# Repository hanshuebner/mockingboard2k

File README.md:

# mockingboard2k - Mockingboard compatible Apple II sound card

This Mockingboard clone uses SMD parts for all modern components.  The KiCAD
project was cloned from the Apple II 32-GPIO Card by Scott Alfter.

[Schematic](mockingboard2k.pdf)

Please make sure that you're using 6522A VIAs.  6522 chips often don't work
with the Phi2 generation circuit that is present on this board.

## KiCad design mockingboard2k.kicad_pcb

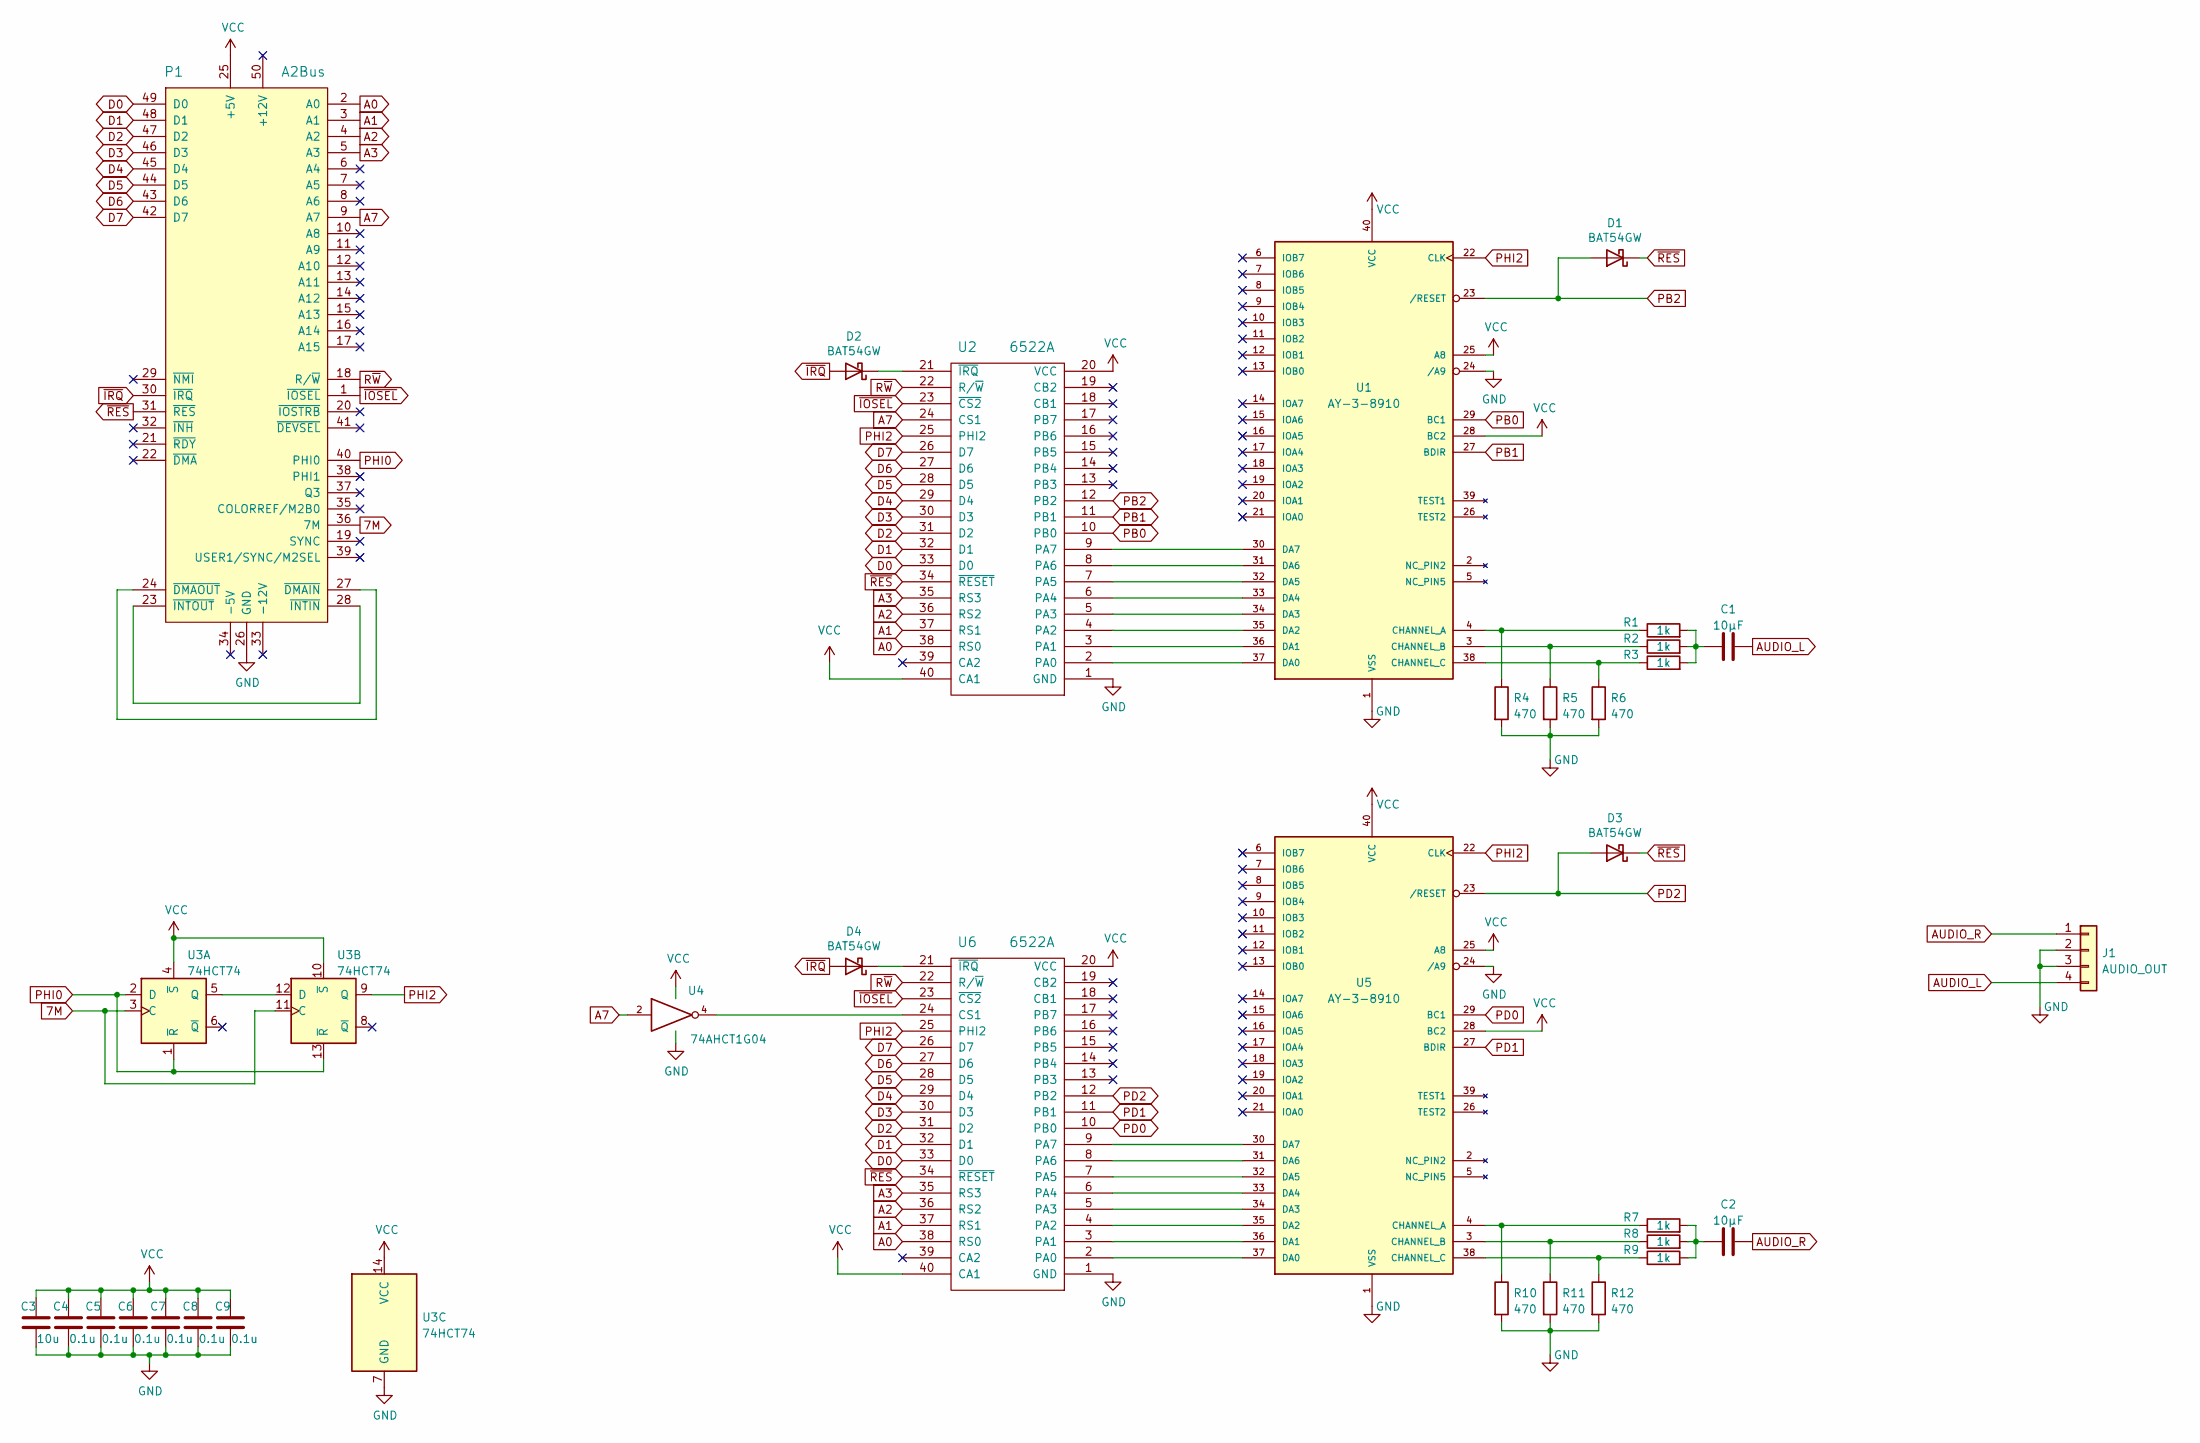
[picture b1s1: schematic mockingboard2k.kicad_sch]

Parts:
C1, C2: 10μF; C_0805_2012Metric; LCSC C2835555
C3: 10u; C_0805_2012Metric; LCSC C2830722
C4, C5, C6, C7, C8, C9: 0.1u; C_0805_2012Metric; LCSC C2830722
D1, D2, D3, D4: BAT54GW; D_SOD-123; Mfr PN BAT54GWJ; LCSC C77343
J1: AUDIO_OUT; PinSocket_1x04_P2.54mm_Horizontal
P1: A2Bus; Male_Card-Edge_50_pin__100_mil
R1, R2, R3, R7, R8, R9: 1k; R_0805_2012Metric; LCSC C325761
R4, R5, R6, R10, R11, R12: 470; R_0805_2012Metric; LCSC C269542
U1, U5: AY-3-8910; DIP-40_W15.24mm
U2, U6: 6522A; DIP-40_W15.24mm; Mfr PN W65C22S6TPG-14
U3: 74HCT74; TSSOP-14_4.4x5mm_P0.65mm; LCSC C8164
U4: 74AHCT1G04; 74AHCT1G04W5-7; LCSC C460498

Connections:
7M: P1.36 (7M), U3.3 (C), U3.11 (C)
A0: P1.2 (A0), U2.38 (RS0), U6.38 (RS0)
A1: P1.3 (A1), U2.37 (RS1), U6.37 (RS1)
A2: P1.4 (A2), U2.36 (RS2), U6.36 (RS2)
A3: P1.5 (A3), U2.35 (RS3), U6.35 (RS3)
A7: P1.9 (A7), U2.24 (CS1), U4.2
AUDIO_L: C1.2, J1.4
AUDIO_R: C2.2, J1.1
D0: P1.49 (D0), U2.33 (D0), U6.33 (D0)
D1: P1.48 (D1), U2.32 (D1), U6.32 (D1)
D2: P1.47 (D2), U2.31 (D2), U6.31 (D2)
D3: P1.46 (D3), U2.30 (D3), U6.30 (D3)
D4: P1.45 (D4), U2.29 (D4), U6.29 (D4)
D5: P1.44 (D5), U2.28 (D5), U6.28 (D5)
D6: P1.43 (D6), U2.27 (D6), U6.27 (D6)
D7: P1.42 (D7), U2.26 (D7), U6.26 (D7)
GND: C3.2, C4.2, C5.2, C6.2, C7.2, C8.2, C9.2, J1.2, J1.3, P1.26 (GND), R4.2, R5.2, R6.2, R10.2, R11.2, R12.2, U1.1 (VSS), U1.24 (/A9), U2.1 (GND), U3.7 (GND), U4.3 (GND), U5.1 (VSS), U5.24 (/A9), U6.1 (GND)
unnamed: C1.1, R1.2, R2.2, R3.2
unnamed: C2.1, R7.2, R8.2, R9.2
unnamed: D2.1 (K), U2.21 (~IRQ)
unnamed: D4.1 (K), U6.21 (~IRQ)
unnamed: P1.23 (~INTOUT), P1.28 (~INTIN)
unnamed: P1.24 (~DMAOUT), P1.27 (~DMAIN)
unnamed: R1.1, R4.1, U1.4 (CHANNEL_A)
unnamed: R2.1, R5.1, U1.3 (CHANNEL_B)
unnamed: R3.1, R6.1, U1.38 (CHANNEL_C)
unnamed: R7.1, R10.1, U5.4 (CHANNEL_A)
unnamed: R8.1, R11.1, U5.3 (CHANNEL_B)
unnamed: R9.1, R12.1, U5.38 (CHANNEL_C)
unnamed: U1.30 (DA7), U2.9 (PA7)
unnamed: U1.31 (DA6), U2.8 (PA6)
unnamed: U1.32 (DA5), U2.7 (PA5)
unnamed: U1.33 (DA4), U2.6 (PA4)
unnamed: U1.34 (DA3), U2.5 (PA3)
unnamed: U1.35 (DA2), U2.4 (PA2)
unnamed: U1.36 (DA1), U2.3 (PA1)
unnamed: U1.37 (DA0), U2.2 (PA0)
unnamed: U3.5 (Q), U3.12 (D)
unnamed: U4.4, U6.24 (CS1)
unnamed: U5.30 (DA7), U6.9 (PA7)
unnamed: U5.31 (DA6), U6.8 (PA6)
unnamed: U5.32 (DA5), U6.7 (PA5)
unnamed: U5.33 (DA4), U6.6 (PA4)
unnamed: U5.34 (DA3), U6.5 (PA3)
unnamed: U5.35 (DA2), U6.4 (PA2)
unnamed: U5.36 (DA1), U6.3 (PA1)
unnamed: U5.37 (DA0), U6.2 (PA0)
PB0: U1.29 (BC1), U2.10 (PB0)
PB1: U1.27 (BDIR), U2.11 (PB1)
PB2: D1.2 (A), U1.23 (/RESET), U2.12 (PB2)
PD0: U5.29 (BC1), U6.10 (PB0)
PD1: U5.27 (BDIR), U6.11 (PB1)
PD2: D3.2 (A), U5.23 (/RESET), U6.12 (PB2)
PHI0: P1.40 (PHI0), U3.1 (~R), U3.2 (D), U3.13 (~R)
PHI2: U1.22 (CLK), U2.25 (PHI2), U3.9 (Q), U5.22 (CLK), U6.25 (PHI2)
R~W: P1.18 (R/~W), U2.22 (R/~W), U6.22 (R/~W)
VCC: C3.1, C4.1, C5.1, C6.1, C7.1, C8.1, C9.1, P1.25 (+5V), U1.25 (A8), U1.28 (BC2), U1.40 (VCC), U2.20 (VCC), U2.40 (CA1), U3.4 (~S), U3.10 (~S), U3.14 (VCC), U4.5 (VCC), U5.25 (A8), U5.28 (BC2), U5.40 (VCC), U6.20 (VCC), U6.40 (CA1)
~IOSEL: P1.1 (~IOSEL), U2.23 (~CS2), U6.23 (~CS2)
~IRQ: D2.2 (A), D4.2 (A), P1.30 (~IRQ)
~RES: D1.1 (K), D3.1 (K), P1.31 (~RES), U2.34 (~RESET), U6.34 (~RESET)

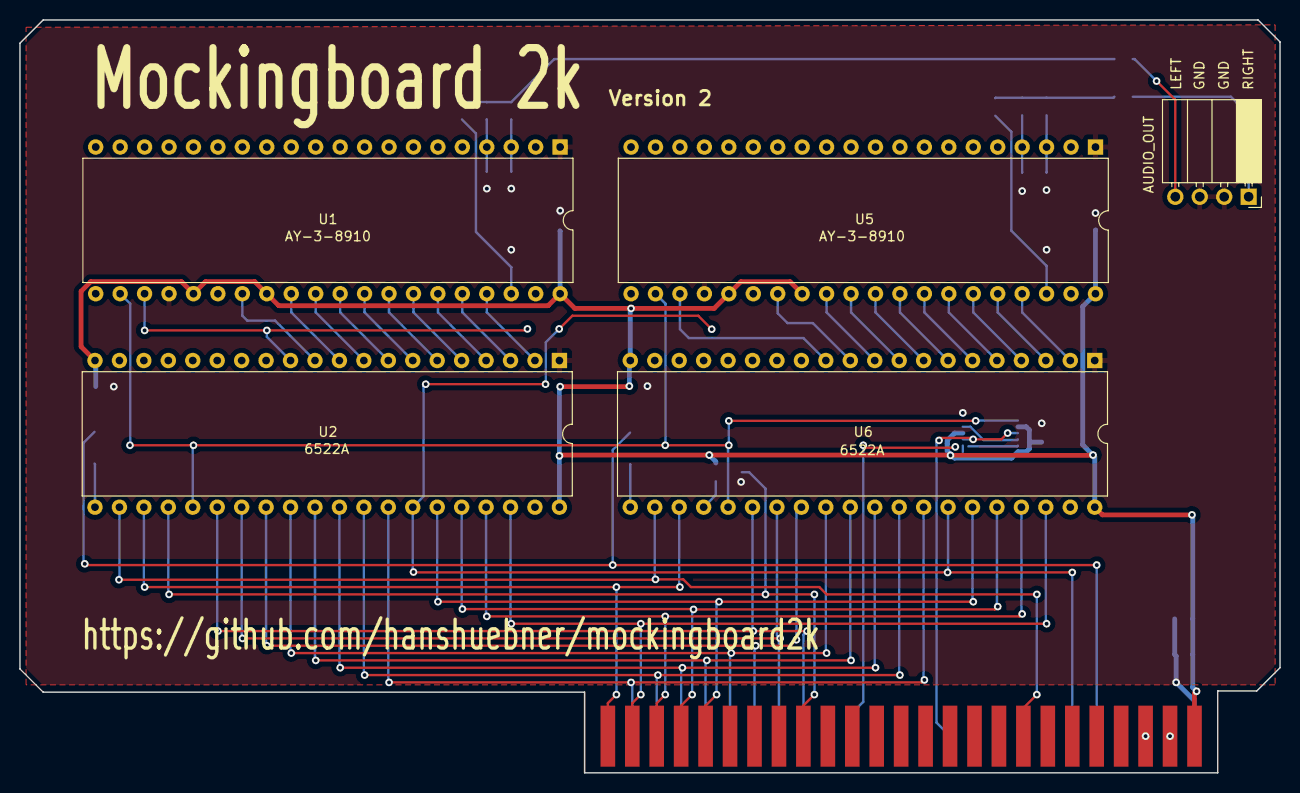
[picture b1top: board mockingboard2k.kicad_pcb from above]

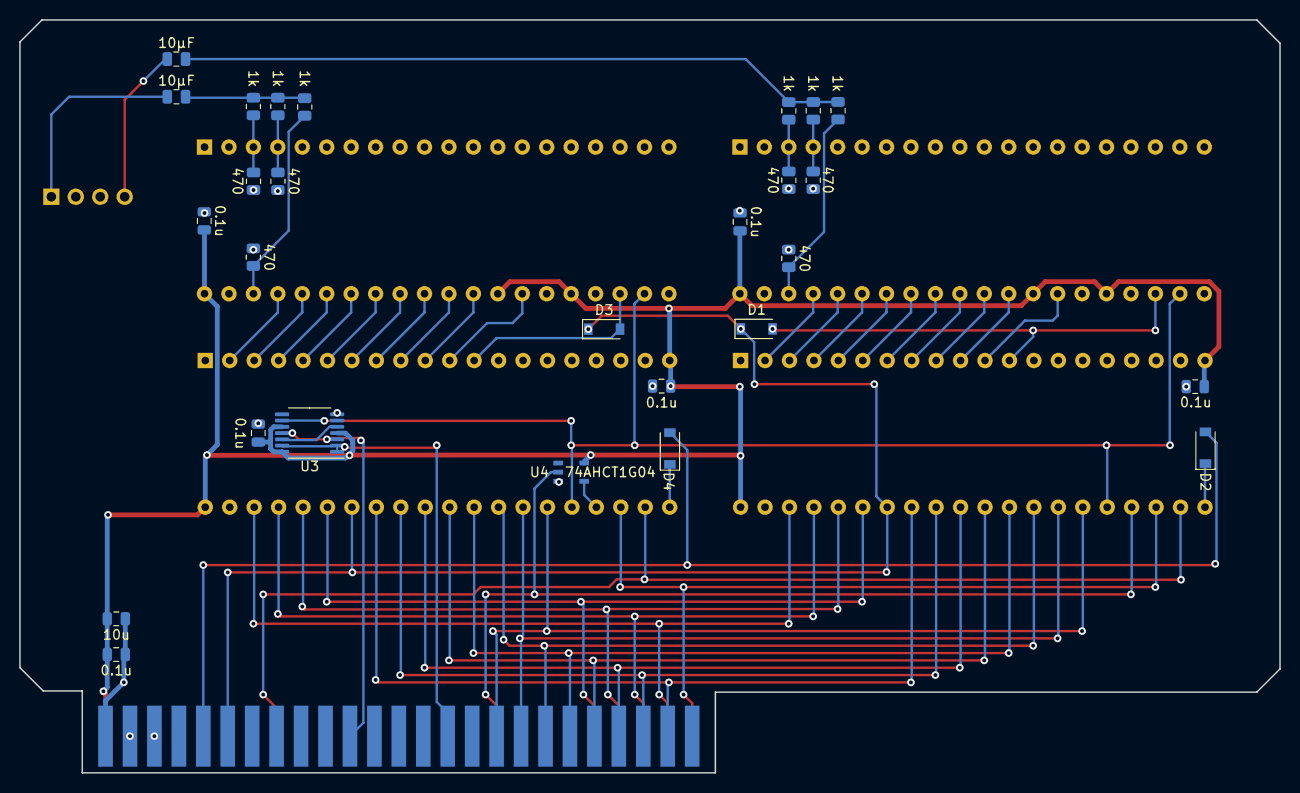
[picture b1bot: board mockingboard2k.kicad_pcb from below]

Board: 2 copper layers, 130.9 x 78.2 mm, 33 parts (27 on the bottom side), 60 nets.

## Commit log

2018-09-14 more routing
2018-09-16 routing complete
2018-09-16 shrink card a bit
2018-09-17 trim 150 mils off edge connector, generate gerbers
2018-09-17 add documentation
2018-09-17 add Schottky diodes on IRQ outputs for W65C22S
2018-09-17 add a PDF of the schematic
2018-09-18 edge connector revised
2022-03-26 Mockingboard with delay-based Phi2
2022-03-26 All-SMD version
2022-03-26 Internalizing libs
2022-03-26 Add libs
2022-03-26 Version 1 ordered at JLCPCB
2022-05-04 Tweaks
2022-05-04 6522A(!)
2022-05-04 README.me
2022-05-05 Fixes to 3D model, README update, gerbers update
2022-05-05 Add schematic PDF

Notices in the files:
parts and their libraries:
Copyright 2021 Accelerated Designs. All rights reserved.
